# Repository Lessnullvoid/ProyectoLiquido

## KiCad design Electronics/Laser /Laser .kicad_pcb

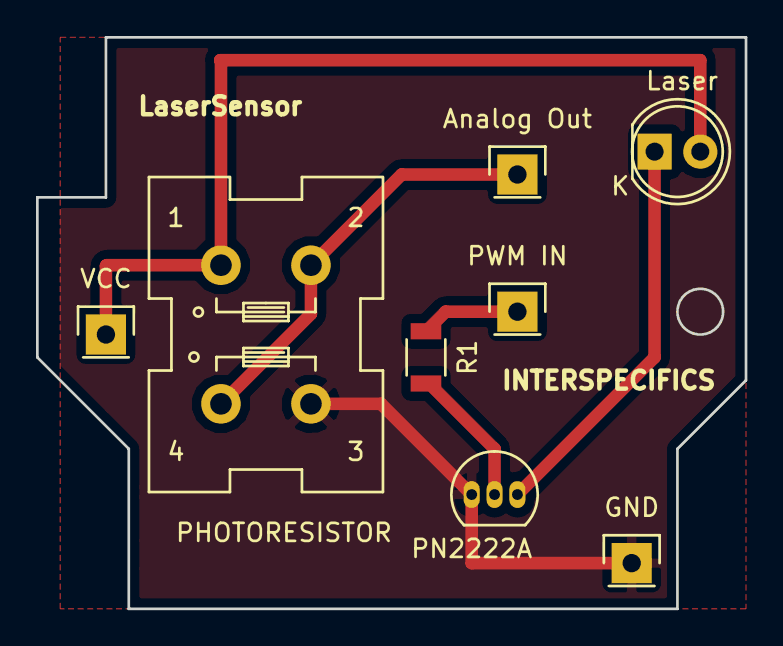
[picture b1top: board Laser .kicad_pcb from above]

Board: 2 copper layers, 39.4 x 31.8 mm, 8 parts (0 on the bottom side), 6 nets.

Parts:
D1: Laser; LED-5MM
P1: Analog Out; Pin_Header_Straight_1x01
P2: PWM IN; Pin_Header_Straight_1x01
P3: VCC; Pin_Header_Straight_1x01
P4: GND; Pin_Header_Straight_1x01
Q1: PN2222A; TO-92_Inline_Narrow_Oval
R1: R; R_1206
U1: PHOTORESISTOR; CommonModeChoke_WuerthType-WE-CMB_Size-S

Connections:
GND: P4.1, Q1.1, U1.3
unnamed: D1.1, Q1.3
unnamed: P1.1, U1.2, U1.4
unnamed: P2.1, R1.1
unnamed: Q1.2, R1.2
VCC: D1.2, P3.1, U1.1

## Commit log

2016-03-18 EEG data sets on csv
2016-03-23 pruebas de visualizacion de canales y sesiones
2016-03-23 gitignore
2016-03-23 caches visualization into PGraphics
2016-03-23 show all signals from each session
2016-03-23 shows all sessions for a given signal
2016-03-23 full alternative drawing modes
2016-03-23 clean the ambiental light signal from the sensor
2016-03-24 update variable name
2016-03-24 max and avg filters on data for galleta_test
2016-03-24 notes
2016-03-25 add LPF. cleans pgraphic setup
2016-03-25 removes Luisa data
2016-03-25 renames marco file
2016-03-25 STL Test
2016-03-25 filter data
2016-03-25 move raw eeg data to own directory
2016-03-25 cleans up extra comma from header of filtered csv files
2016-03-25 changes in Processing files to read new/filtered csv files
2016-03-25 generates STL model: gives bottom and thickness
2016-03-25 fixes model x,y dimension math
2016-03-26 average 5 laser sensor values
2016-03-27 added extra lasers
2016-03-27 manual bottom for stl
2016-03-27 puts plugs at bottom of 3d stl model
2016-03-28 parametrizable width
2016-04-07 new data sets
2016-04-07 laser sensor circuit
2016-04-07 update files
2016-05-03 added motor library
2016-05-03 tabs
2016-05-03 using arrays for everything
2016-06-04 with hole at bottom instead of cubes
2016-06-04 renames sketches _Test -> _Generator
2016-06-04 removes stls from repository
2016-06-11 added new data sets
2016-06-16 remove sets
2016-06-17 Actualización de columnas
2016-06-25 adds serial communication writing capabilities
2016-06-26 using short for average serial sending
2016-06-26 sending scaled down sensor value
2016-06-26 send raw, pre-average, values
2016-07-09 clean data sets
2016-07-16 control de velocidad
2016-07-20 códigos actualizados
2018-06-08 visuales con bandas EEG
